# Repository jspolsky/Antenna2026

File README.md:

Future Turtles 2026 Public LED Display
====

In 2024 we
* upped the number of whips to 24
* got rid of the central antenna
* improved cabling via daisy chaining

For 2026 we
* made the box at the foot of each whip smaller
* hard wired those boxes instead of using external connectors
* used two sources of power so that 16awg wires are adequate
* implemented a bird game

2026 TODO LIST:
===============
- [ ] Continue to study intermittent freezes
        - [ ] Consider a watchdog https://github.com/TeensyUser/doc/wiki/The-Watchdog-timer
- [x] Fix 50 foot cable issues (see below)
- [x] Test game rendering with actual whips
- [x] Replace 600W power supplies with 300W
    - [x] Test temperature inside power packs
    - [x] Install new mounting plates     
- [x] Provide a way to separate left and right halves of whip control harness
    - [x] Modify setup documentation accordingly
- [ ] Implement game button
    - [x] Revise controller PCB to expose more pins (sent to JLCPCB)
    - [x] Rebuild controllers
    - [x] Cable to game button
    - [ ] Game button mounting hardware 
- [x] Finalize game code and flash it onto every MCU
- [ ] Set up a nice spare parts box

50-FOOT CABLE FIX
=================

Yes, the cable length is absolutely the problem. Here's what's happening and how to fix it.

## Why It Breaks with a Long Cable

A 50' cable introduces two nasty problems:

**1. It becomes an antenna.** The long wire efficiently picks up EMI from nearby mains wiring, motors, lighting, etc. This induced noise gets injected directly onto your input pin, causing phantom button presses or preventing real ones from registering cleanly.

**2. Capacitance loads the pullup.** Typical unshielded cable has ~30pF/foot of capacitance. At 50 feet that's ~1,500pF. The Teensy 4.1's internal pullup is a weak ~22kΩ–47kΩ. That RC combination means the pin rises very slowly when the button is released — well outside the clean logic thresholds the chip expects, causing unreliable reads.

---

## Fixes (use in combination)

**1. Add an external pullup resistor (most important)**

Replace the weak internal pullup with a strong external one. Solder a resistor directly from the signal pin to 3.3V *on the Teensy end* of the cable.

| Cable length | Recommended value |
|---|---|
| Up to ~10ft | 10kΩ (internal pullup is fine) |
| ~50ft | **1kΩ – 4.7kΩ** |

In your code, switch from `INPUT_PULLUP` to plain `INPUT` since you're now providing your own pullup.

**2. Add a bypass capacitor**

Place a **100nF ceramic capacitor** from the signal line to GND, right at the Teensy's pin header. This forms a low-pass RC filter with the series resistance of the cable, killing high-frequency noise before it reaches the pin.

```
3.3V
 |
[1kΩ–4.7kΩ]  ← external pullup
 |
 +----[Teensy Pin]
 |
[100nF]       ← bypass cap to GND
 |
GND
```

**3. Use shielded cable**

A shielded cable (e.g., mic cable, alarm wire, or screened 2-conductor) dramatically reduces the antenna effect. Connect the shield to GND at **one end only** (the Teensy end) to avoid ground loops.

**4. Improve software debouncing**

With a long cable you'll want a more generous debounce window even after the hardware fixes. A 20–50ms debounce is reasonable. If you're not already using a library, the [Bounce2](https://github.com/thomasfredericks/Bounce2) library works great on Teensy:

```cpp
#include <Bounce2.h>

Bounce button = Bounce();

void setup() {
  pinMode(BUTTON_PIN, INPUT);       // external pullup, so just INPUT
  button.attach(BUTTON_PIN);
  button.interval(25);              // 25ms debounce
}

void loop() {
  button.update();
  if (button.fell()) {              // button pressed (HIGH → LOW)
    // do the thing
  }
}
```

---

## Quick Summary

The combination of a **1–4.7kΩ external pullup** + **100nF cap to GND at the Teensy pin** will almost certainly solve this. Shielded cable and software debouncing are good additions if you're still seeing noise after that.

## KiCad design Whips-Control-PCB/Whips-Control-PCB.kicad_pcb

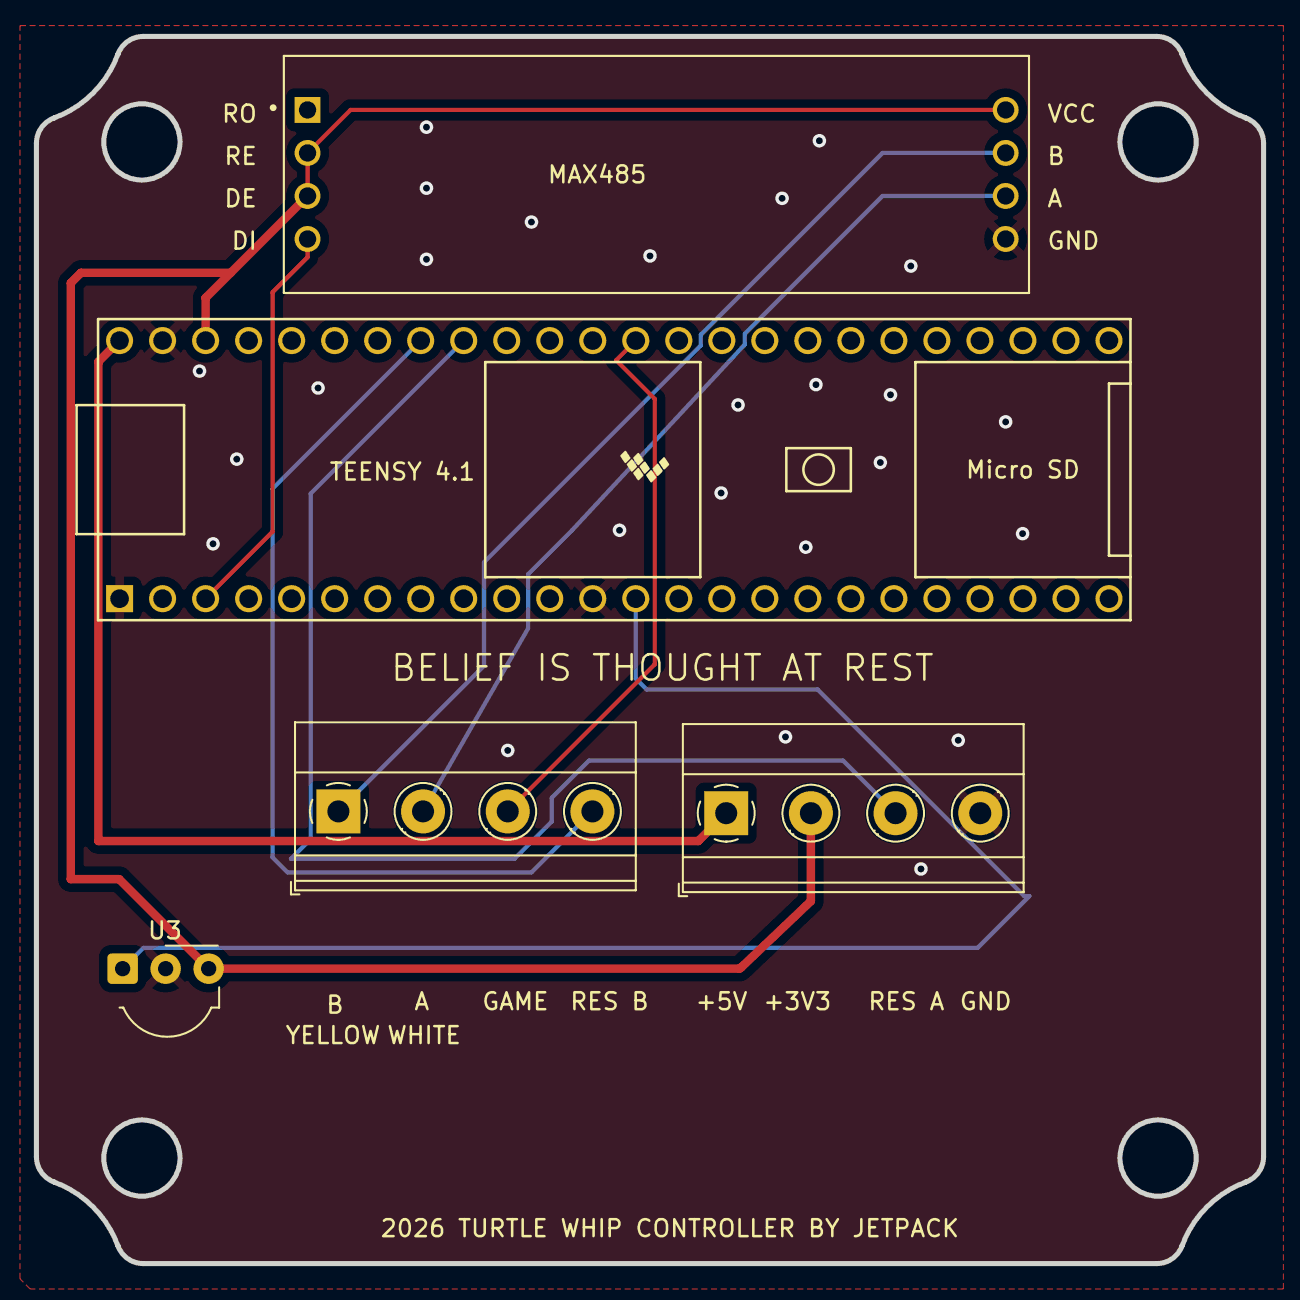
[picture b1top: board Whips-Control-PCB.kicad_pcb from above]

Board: 2 copper layers, 72.5 x 72.5 mm, 5 parts (0 on the bottom side), 10 nets.

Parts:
J1, J4: Conn_01x04_Pin; TerminalBlock_Phoenix_MKDS-1,5-4_1x04_P5.00mm_Horizontal
MAX485: MAX485E; Max485-Module
TEENSY 4.1: Teensy4.1_Minimal; Teensy41_Minimal
U3: TSOP341xx; Vishay_MOLD-3Pin

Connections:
+3.3V: J1.2, MAX485.2 (~RE), MAX485.3 (DE), MAX485.8 (VCC), TEENSY 4.1.46 (3V3), U3.3 (Vs)
+5V: J1.1, TEENSY 4.1.48 (VIN)
/A: J4.2, MAX485.6 (A)
/B: J4.1, MAX485.7 (B)
/DI: MAX485.4 (DI), TEENSY 4.1.3 (1_TX1_CTX2_MISO1)
/GAME: J4.3, TEENSY 4.1.36 (14_A0_TX3_SPDIF_OUT)
/IR: TEENSY 4.1.13 (11_MOSI_CTX1), U3.1 (OUT)
/RESERVEDA: J1.3, TEENSY 4.1.40 (18_A4_SDA)
/RESERVEDB: J4.4, TEENSY 4.1.41 (19_A5_SCL)
GND: J1.4, MAX485.5 (GND), TEENSY 4.1.1 (GND), TEENSY 4.1.12 (10_CS_MQSR), TEENSY 4.1.47 (GND), U3.2 (GND)

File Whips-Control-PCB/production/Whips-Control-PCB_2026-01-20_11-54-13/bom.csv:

Designator,Footprint,Quantity,Value,LCSC Part #
"J1, J4","TerminalBlock_Phoenix_MKDS-1,5-4_1x04_P5.00mm_Horizontal",2,Conn_01x04_Pin,
MAX485,Max485-Module,1,MAX485E,
TEENSY 4.1,Teensy41_Minimal,1,Teensy4.1_Minimal,
U3,Vishay_MOLD-3Pin,1,TSOP341xx,

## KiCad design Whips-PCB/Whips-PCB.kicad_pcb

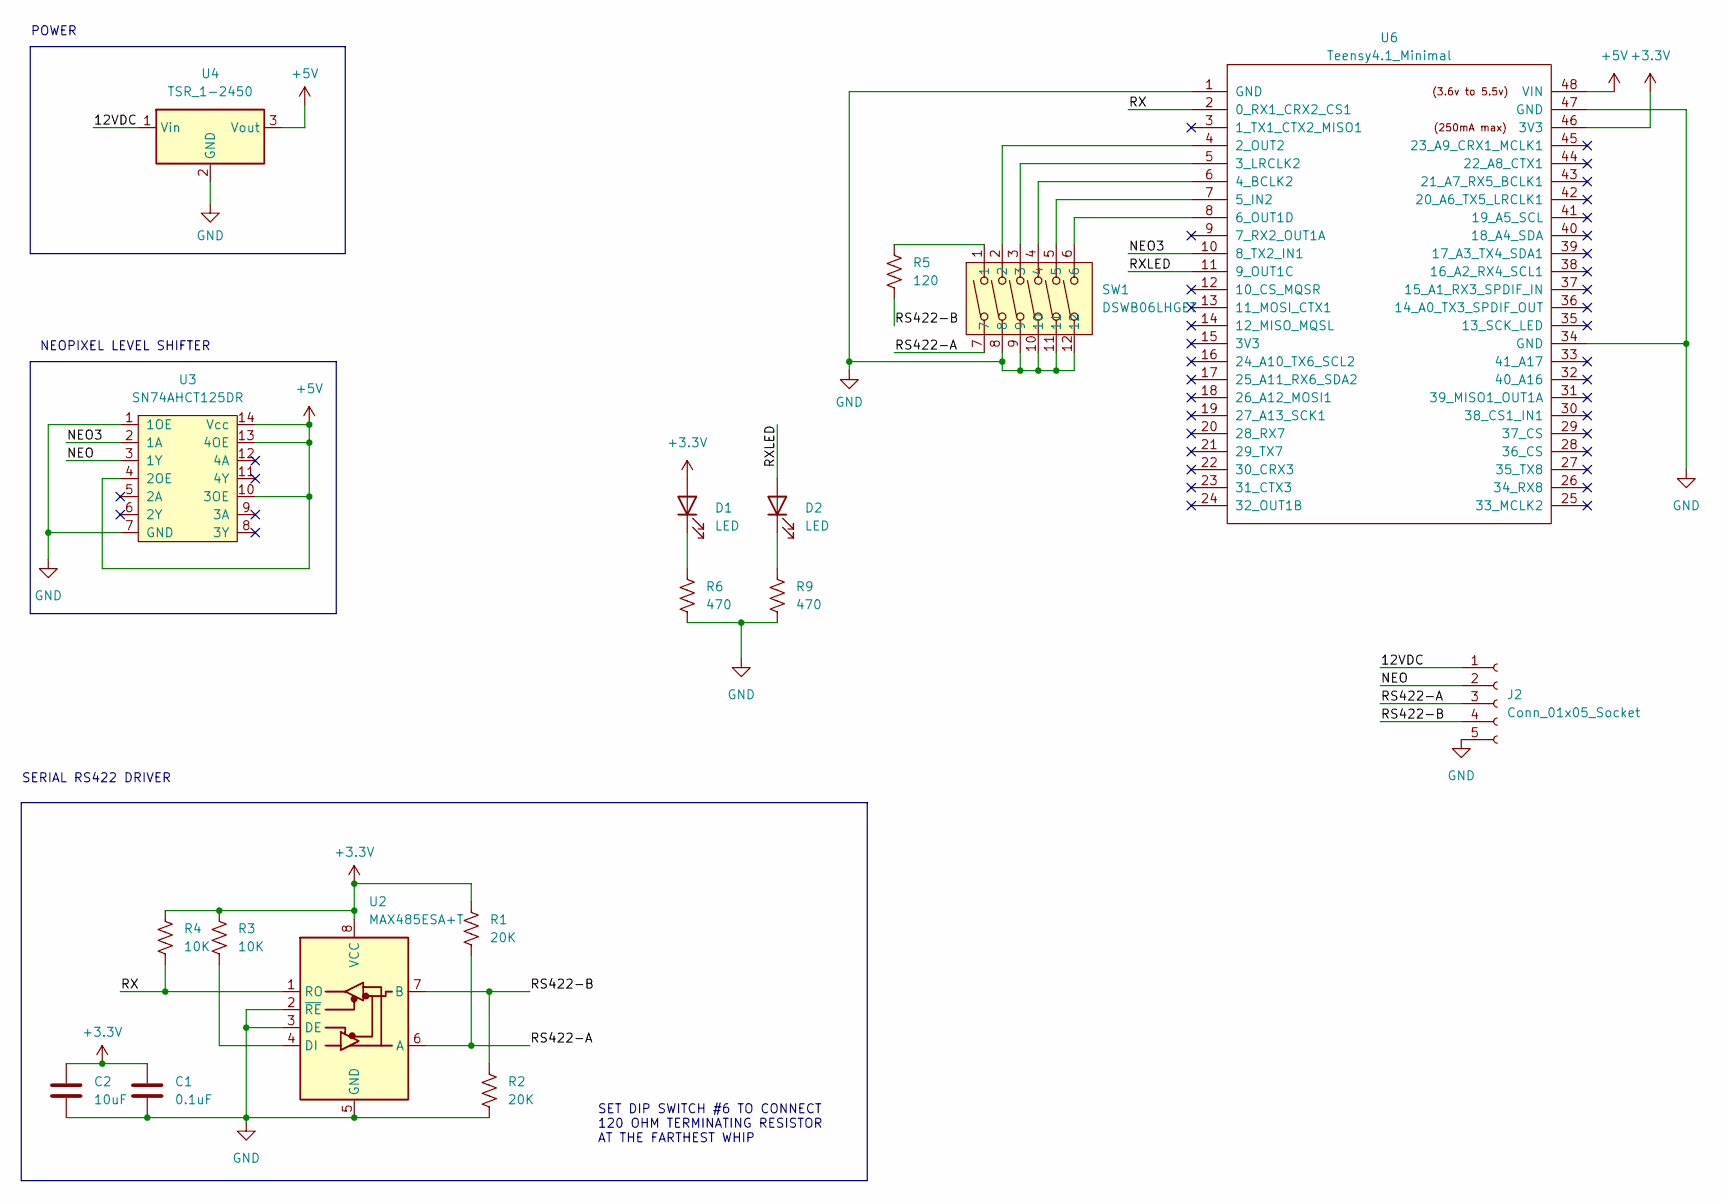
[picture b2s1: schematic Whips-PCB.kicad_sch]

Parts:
C1: 0.1uF; C_0402_1005Metric; LCSC C1525
C2: 10uF; C_0402_1005Metric; LCSC C15525
D1: LED; LED_0603_1608Metric; LCSC C2286
D2: LED; LED_0603_1608Metric; LCSC C2290
J2: Conn_01x05_Socket; Dorabo_DB103-5.0-5P-GN-S; LCSC C395854
R1, R2: 20K; R_0603_1608Metric; LCSC C4184
R3, R4: 10K; R_0603_1608Metric; LCSC C25804
R5: 120; R_0402_1005Metric; LCSC C25079
R6, R9: 470; R_0402_1005Metric; LCSC C25117
SW1: DSWB06LHGET; DongGuan_DSWB06LHGET_6_PIN_DIP; LCSC Part C99416
U2: MAX485ESA+T; SOIC-8_3.9x4.9mm_P1.27mm; LCSC C19738
U3: SN74AHCT125DR; SOIC-14_3.9x8.7mm_P1.27mm; LCSC C155176
U4: TSR_1-2450; Converter_DCDC_TRACO_TSR-1_THT; LCSC DNP
U6: Teensy4.1_Minimal; Teensy41_Minimal; LCSC DNP

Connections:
+3.3V: C1.1, C2.1, D1.2 (A), R1.1, R3.1, R4.1, U2.8 (VCC), U6.46 (3V3)
+5V: U3.4 (2OE), U3.10 (3OE), U3.13 (4OE), U3.14 (Vcc), U4.3 (Vout), U6.48 (VIN)
/12VDC: J2.1, U4.1 (Vin)
/NEO: J2.2, U3.3 (1Y)
/NEO3: U3.2 (1A), U6.10 (8_TX2_IN1)
/RS422-A: J2.3, R1.2, SW1.7, U2.6 (A)
/RS422-B: J2.4, R2.2, R5.2, U2.7 (B)
/RX: R4.2, U2.1 (RO), U6.2 (0_RX1_CRX2_CS1)
/RXLED: D2.2 (A), U6.11 (9_OUT1C)
GND: C1.2, C2.2, J2.5, R2.1, R6.2, R9.2, SW1.8, SW1.9, SW1.10, SW1.11, SW1.12, U2.2 (~RE), U2.3 (DE), U2.5 (GND), U3.1 (1OE), U3.7 (GND), U4.2 (GND), U6.1 (GND), U6.34 (GND), U6.47 (GND)
unnamed: D1.1 (K), R6.1
unnamed: D2.1 (K), R9.1
unnamed: R5.1, SW1.1
unnamed: R3.2, U2.4 (DI)
unnamed: SW1.2, U6.4 (2_OUT2)
unnamed: SW1.3, U6.5 (3_LRCLK2)
unnamed: SW1.4, U6.6 (4_BCLK2)
unnamed: SW1.5, U6.7 (5_IN2)
unnamed: SW1.6, U6.8 (6_OUT1D)

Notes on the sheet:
POWER
SERIAL RS422 DRIVER
NEOPIXEL LEVEL SHIFTER
SET DIP SWITCH #6 TO CONNECT 120 OHM TERMINATING RESISTOR AT THE FARTHEST WHIP

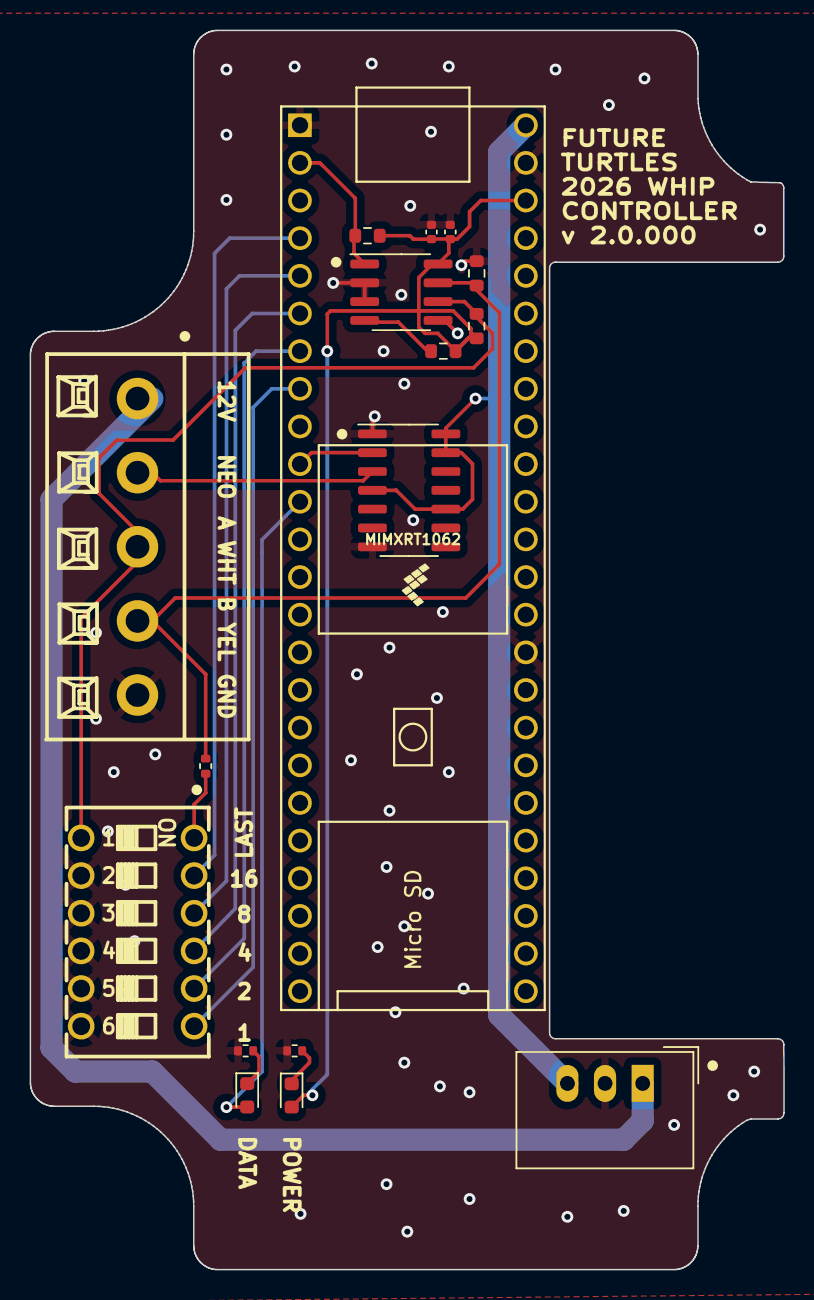
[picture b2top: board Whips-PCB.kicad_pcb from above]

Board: 2 copper layers, 50.8 x 83.6 mm, 17 parts (0 on the bottom side), 19 nets.

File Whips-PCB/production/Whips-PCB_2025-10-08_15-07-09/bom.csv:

Designator,Footprint,Quantity,Value,LCSC Part #
C1,0402,1,0.1uF,C1525
C2,0402,1,10uF,C15525
D1,0603,1,LED,C2286
D2,0603,1,LED,C2290
J2,Dorabo_DB103-5.0-5P-GN-S,1,Conn_01x05_Socket,C395854
"R1, R2",0603,2,20K,C4184
"R3, R4",0603,2,10K,C25804
R5,0402,1,120,C25079
"R6, R9",0402,2,470,C25117
SW1,DongGuan_DSWB06LHGET_6_PIN_DIP,1,DSWB06LHGET,C99416
U2,SOIC-8_3.9x4.9mm_P1.27mm,1,MAX485ESA+T,C19738
U3,SOIC-14_3.9x8.7mm_P1.27mm,1,SN74AHCT125DR,C155176
U4,Converter_DCDC_TRACO_TSR-1_THT,1,TSR_1-2450,DNP
U6,Teensy41_Minimal,1,Teensy4.1_Minimal,DNP

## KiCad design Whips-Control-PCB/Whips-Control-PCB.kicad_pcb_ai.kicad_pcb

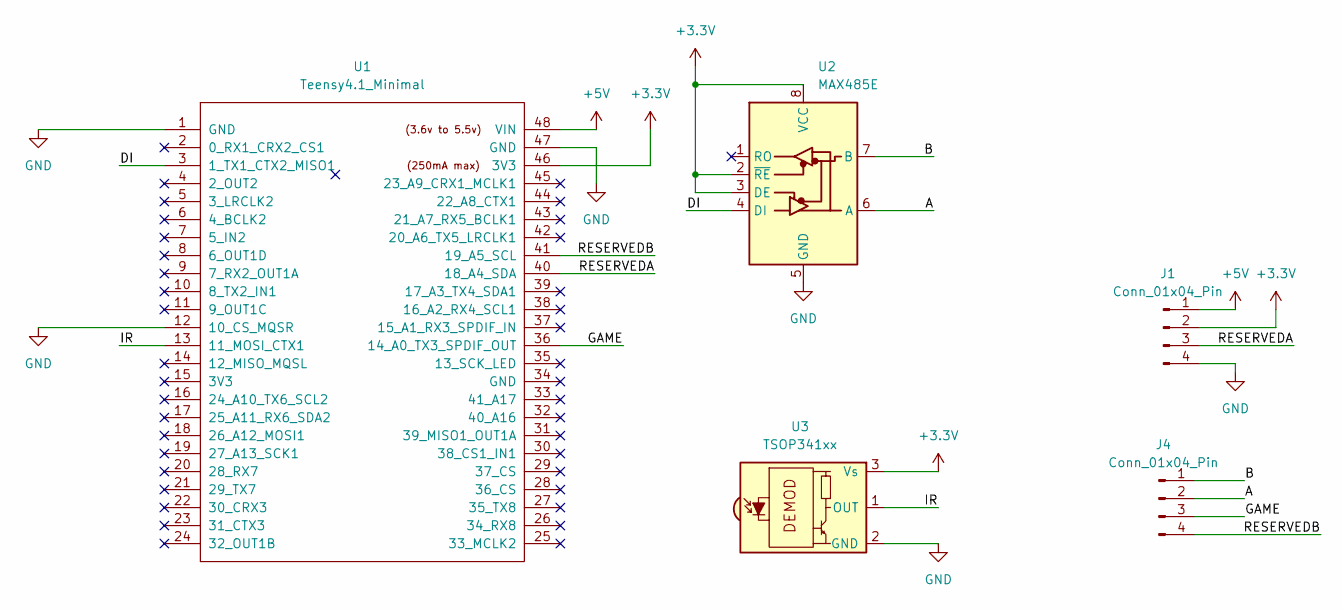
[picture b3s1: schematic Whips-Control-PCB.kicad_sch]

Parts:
J1, J4: Conn_01x04_Pin; TerminalBlock_Phoenix_MKDS-1,5-4_1x04_P5.00mm_Horizontal
U1: Teensy4.1_Minimal; Teensy41_Minimal
U2: MAX485E; Max485-Module
U3: TSOP341xx; Vishay_MOLD-3Pin

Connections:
+3.3V: J1.2, U1.46 (3V3), U2.2 (~RE), U2.3 (DE), U2.8 (VCC), U3.3 (Vs)
+5V: J1.1, U1.48 (VIN)
/A: J4.2, U2.6 (A)
/B: J4.1, U2.7 (B)
/DI: U1.3 (1_TX1_CTX2_MISO1), U2.4 (DI)
/GAME: J4.3, U1.36 (14_A0_TX3_SPDIF_OUT)
/IR: U1.13 (11_MOSI_CTX1), U3.1 (OUT)
/RESERVEDA: J1.3, U1.40 (18_A4_SDA)
/RESERVEDB: J4.4, U1.41 (19_A5_SCL)
GND: J1.4, U1.1 (GND), U1.12 (10_CS_MQSR), U1.47 (GND), U2.5 (GND), U3.2 (GND)

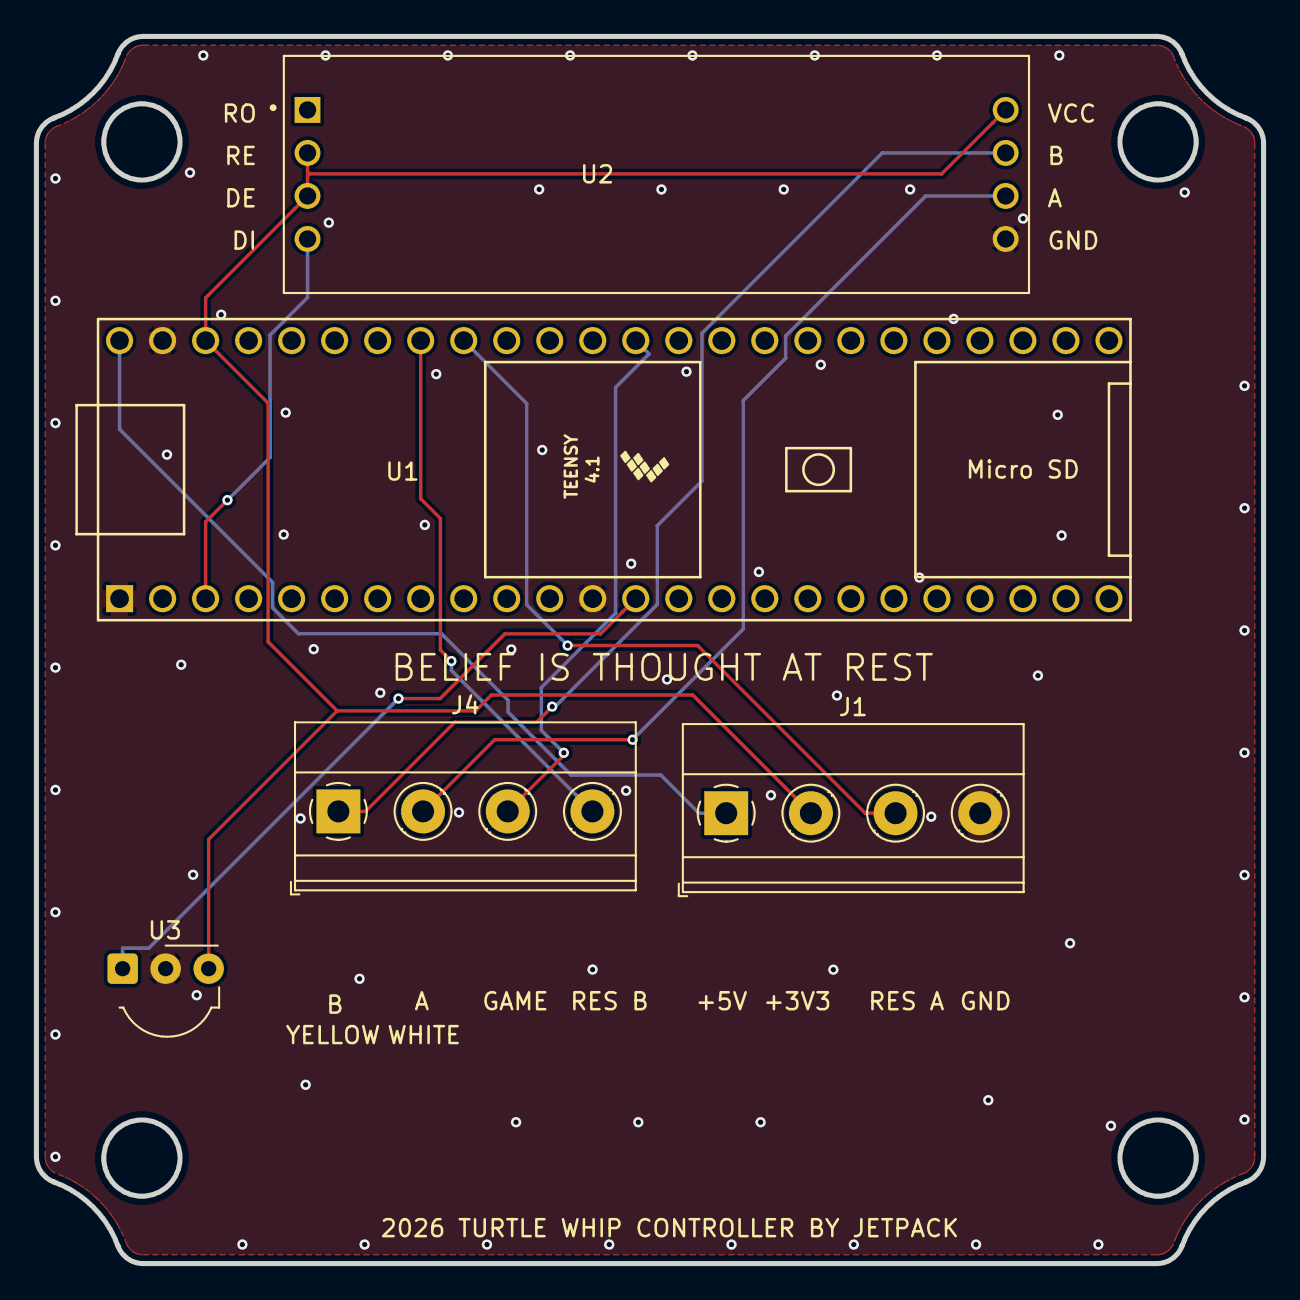
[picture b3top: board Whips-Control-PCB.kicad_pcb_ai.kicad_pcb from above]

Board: 2 copper layers, 72.5 x 72.5 mm, 5 parts (0 on the bottom side), 10 nets.

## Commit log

2026-01-12 Antenna 2026 initiated; new controller PCB
2026-01-12 Getting set up for local preview of whips via USB serial!
2026-01-13 frickin' .DS_Store g'bye
2026-01-13 got a button working...
2026-01-13 Send all commands to visualizer and parse them there
2026-01-14 Working visualizer window! Only does Set Whip Color and Set Brightness so far
2026-01-14 handle the "identify" command
2026-01-14 yep, we can visualize animated gifs no problemo
2026-01-14 better pic of Identify mode in doc
2026-01-14 spec for a flappy bird game
2026-01-14 A reasonable implementation of filppity boids
2026-01-14 fixed some compilation warnings
2026-01-14 support game display on real hardware
2026-01-14 end of game improvements
2026-01-14 death plummet
2026-01-14 narrower hitbox for pipe feels more fair
2026-01-14 render bird in front
2026-01-14 flashing effect on collision
2026-01-14 fixed bug indicating collision with ground
2026-01-15 autoinstall dependencies for monitor
2026-03-02 this is a new PCB for the controller, to fit in a smaller box
2026-03-02 made it actually work on real hardware
2026-03-03 Ability to adjust top and bottom for game
2026-03-03 sine wave if signal lost
2026-03-07 bodge
2026-03-08 experimental fixes for SUB crashes
